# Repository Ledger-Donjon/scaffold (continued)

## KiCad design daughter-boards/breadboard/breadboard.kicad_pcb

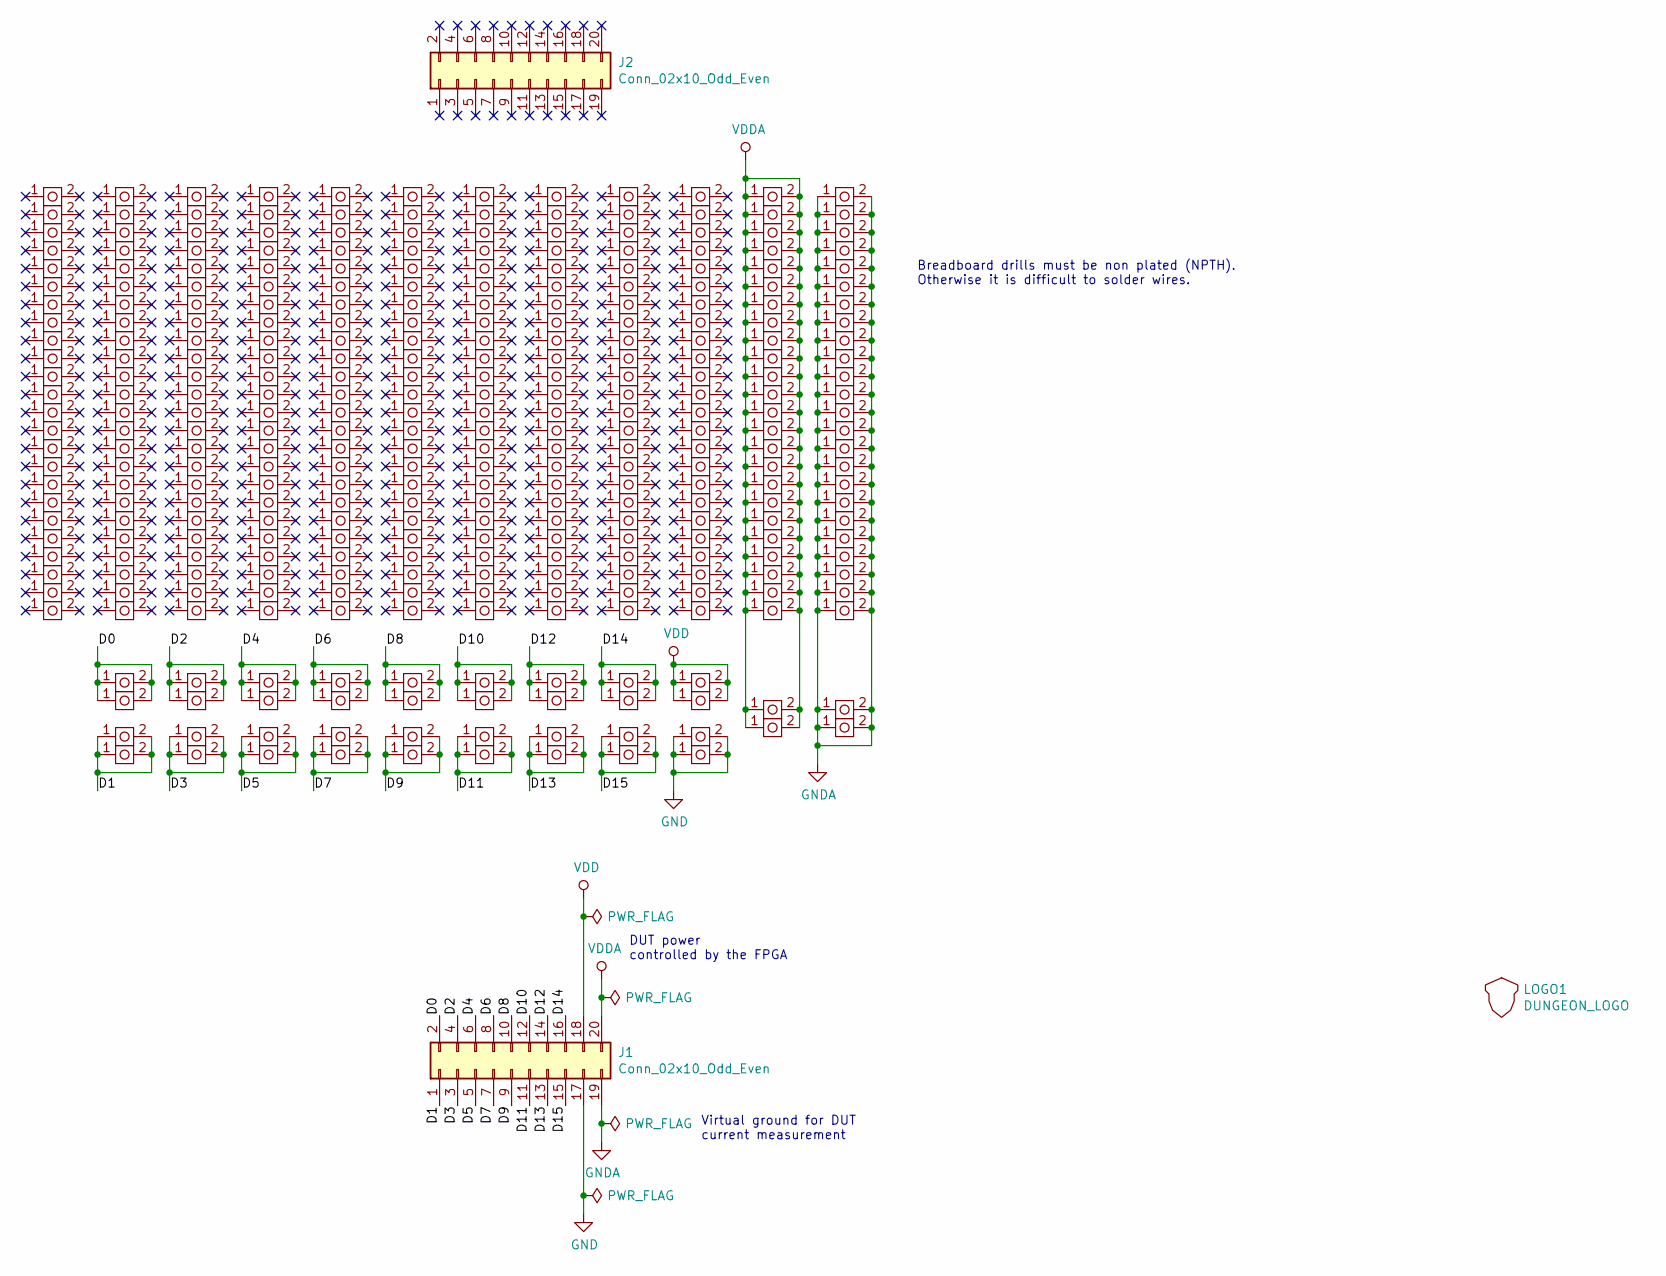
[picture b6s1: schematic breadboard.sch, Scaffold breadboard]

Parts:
J1, J2: Conn_02x10_Odd_Even; PinSocket_2x10_P2.54mm_Vertical
LOGO1: DUNGEON_LOGO; donjon-3000
U1, U2, U3, U4, U5, U6, U7, U8, U9, U10, U11, U12, U13, U14, U15, U16, U17, U18, U19, U20, U21, U22, U23, U24, U25, U26, U27, U28, U29, U30, U31, U32, U33, U34, U35, U36, U37, U38, U39, U40, U41, U42, U43, U44, U45, U46, U47, U48, U49, U50, U51, U52, U53, U54, U55, U56, U57, U58, U59, U60, U61, U62, U63, U64, U65, U66, U67, U68, U69, U70, U71, U72, U73, U74, U75, U76, U77, U78, U79, U80, U81, U82, U83, U84, U85, U86, U87, U88, U89, U90, U91, U92, U93, U94, U95, U96, U97, U98, U99, U100, U101, U102, U103, U104, U105, U106, U107, U108, U109, U110, U111, U112, U113, U114, U115, U116, U117, U118, U119, U120, U121, U122, U123, U124, U125, U126, U127, U128, U129, U130, U131, U132, U133, U134, U135, U136, U137, U138, U139, U140, U141, U142, U143, U144, U145, U146, U147, U148, U149, U150, U151, U152, U153, U154, U155, U156, U157, U158, U159, U160, U161, U162, U163, U164, U165, U166, U167, U168, U169, U170, U171, U172, U173, U174, U175, U176, U177, U178, U179, U180, U181, U182, U183, U184, U185, U186, U187, U188, U189, U190, U191, U192, U193, U194, U195, U196, U197, U198, U199, U200, U201, U202, U203, U204, U205, U206, U207, U208, U209, U210, U211, U212, U213, U214, U215, U216, U217, U218, U219, U220, U221, U222, U223, U224, U225, U226, U227, U228, U229, U230, U231, U232, U233, U234, U235, U236, U237, U238, U239, U240, U241, U242, U243, U244, U245, U246, U247, U248, U249, U250, U251, U252, U253, U254, U255, U256, U257, U258, U259, U260, U261, U262, U263, U264, U265, U266, U267, U268, U269, U270, U271, U272, U273, U274, U275, U276, U277, U278, U279, U280, U281, U282, U283, U284, U285, U286, U287, U288, U289, U290, U291, U292, U293, U294, U295, U296, U297, U298, U299, U300, U301, U302, U303, U304, U305, U306, U307, U308, U309, U310, U311, U312, U313, U314, U315, U316, U317, U318, U319, U320, U321, U322, U323, U324, U325, U326, U327, U328: BREADBOARD_NPTH; TEST_BREADBOARD_RECTANGULAR_NPTH2

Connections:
/D0: J1.2, U297.1, U297.2, U298.1, U298.2
/D1: J1.1, U299.1, U299.2, U300.1, U300.2
/D2: J1.4, U301.1, U301.2, U302.1, U302.2
/D3: J1.3, U303.1, U303.2, U304.1, U304.2
/D4: J1.6, U305.1, U305.2, U306.1, U306.2
/D5: J1.5, U307.1, U307.2, U308.1, U308.2
/D6: J1.8, U309.1, U309.2, U310.1, U310.2
/D7: J1.7, U311.1, U311.2, U312.1, U312.2
/D8: J1.10, U313.1, U313.2, U314.1, U314.2
/D9: J1.9, U315.1, U315.2, U316.1, U316.2
/D10: J1.12, U317.1, U317.2, U318.1, U318.2
/D11: J1.11, U319.1, U319.2, U320.1, U320.2
/D12: J1.14, U321.1, U321.2, U322.1, U322.2
/D13: J1.13, U323.1, U323.2, U324.1, U324.2
/D14: J1.16, U325.1, U325.2, U326.1, U326.2
/D15: J1.15, U327.1, U327.2, U328.1, U328.2
GND: J1.17, U295.1, U295.2, U296.1, U296.2
GNDA: J1.19, U267.1, U267.2, U268.1, U268.2, U269.1, U269.2, U270.1, U270.2, U271.1, U271.2, U272.1, U272.2, U273.1, U273.2, U274.1, U274.2, U275.1, U275.2, U276.1, U276.2, U277.1, U277.2, U278.1, U278.2, U279.1, U279.2, U280.1, U280.2, U281.1, U281.2, U282.1, U282.2, U283.1, U283.2, U284.1, U284.2, U285.1, U285.2, U286.1, U286.2, U287.1, U287.2, U288.1, U288.2, U289.1, U289.2, U290.1, U290.2, U291.1, U291.2, U292.1, U292.2
VDD: J1.18, U293.1, U293.2, U294.1, U294.2
VDDA: J1.20, U241.1, U241.2, U242.1, U242.2, U243.1, U243.2, U244.1, U244.2, U245.1, U245.2, U246.1, U246.2, U247.1, U247.2, U248.1, U248.2, U249.1, U249.2, U250.1, U250.2, U251.1, U251.2, U252.1, U252.2, U253.1, U253.2, U254.1, U254.2, U255.1, U255.2, U256.1, U256.2, U257.1, U257.2, U258.1, U258.2, U259.1, U259.2, U260.1, U260.2, U261.1, U261.2, U262.1, U262.2, U263.1, U263.2, U264.1, U264.2, U265.1, U265.2, U266.1, U266.2

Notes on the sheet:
Virtual ground for DUT current measurement
DUT power controlled by the FPGA
Breadboard drills must be non plated (NPTH). Otherwise it is difficult to solder wires.

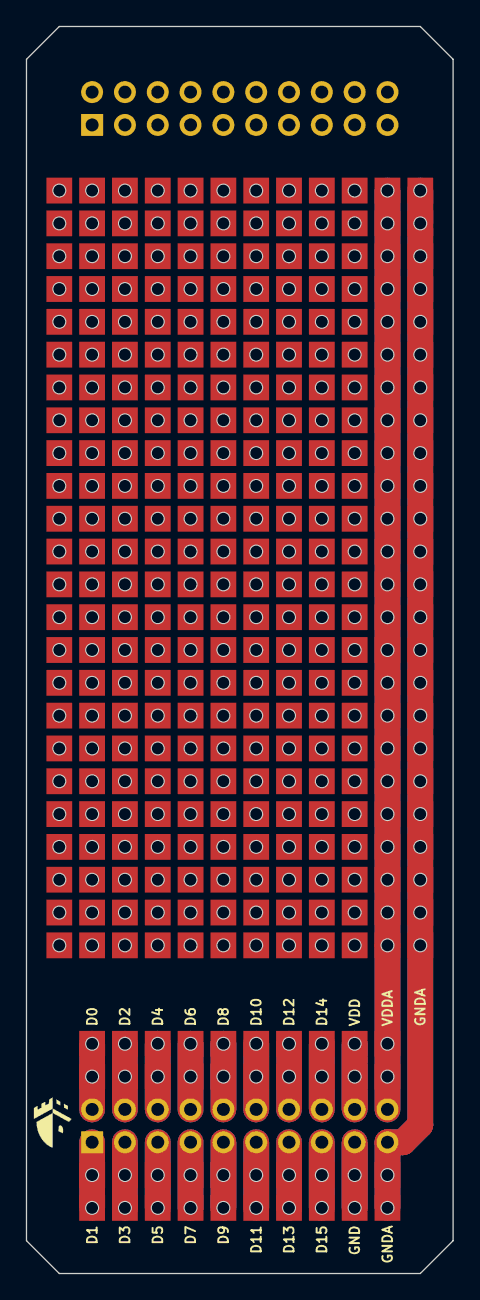
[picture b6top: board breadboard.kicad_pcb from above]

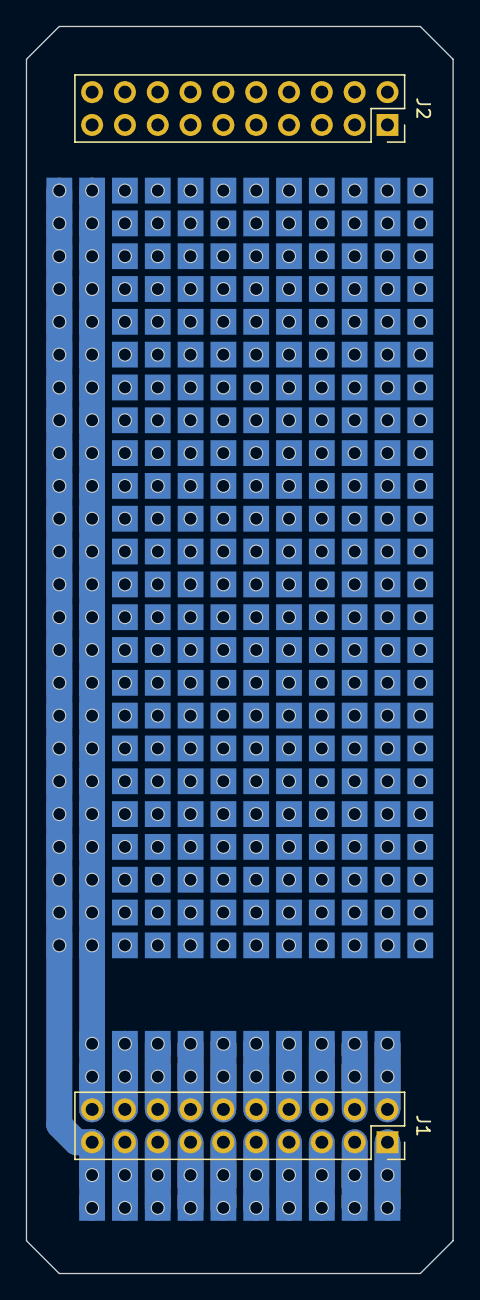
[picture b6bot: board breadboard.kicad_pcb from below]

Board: 2 copper layers, 33.0 x 96.5 mm, 331 parts (2 on the bottom side), 20 nets.

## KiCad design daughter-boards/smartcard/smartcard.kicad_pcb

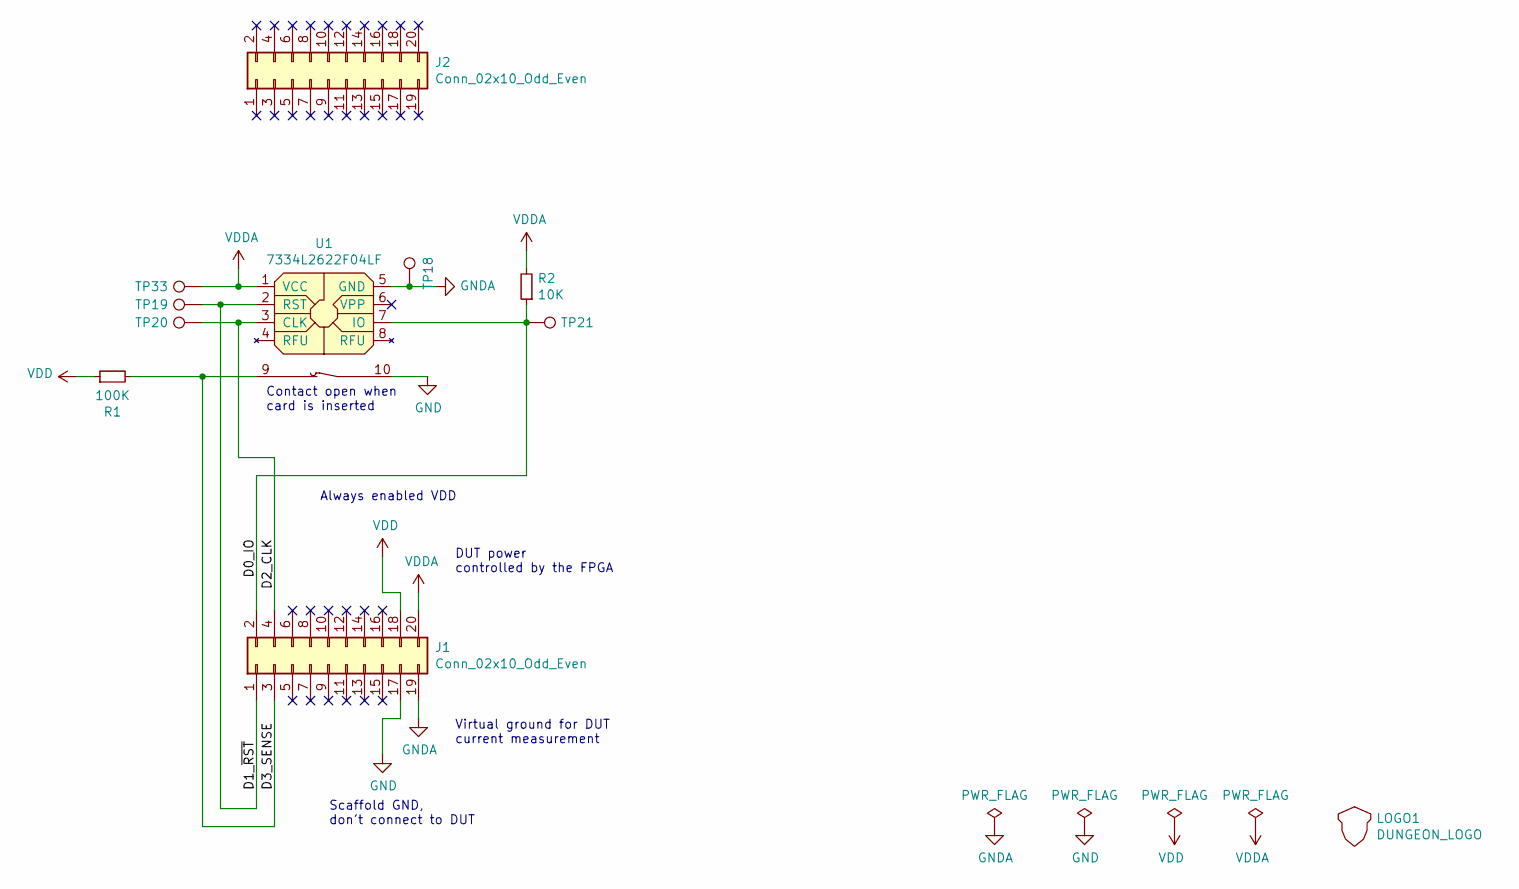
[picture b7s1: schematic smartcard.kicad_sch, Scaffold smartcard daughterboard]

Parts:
J1, J2: Conn_02x10_Odd_Even; PinSocket_2x10_P2.54mm_Vertical
LOGO1: DUNGEON_LOGO; donjon-2000
R1: 100K; R_0603_1608Metric
R2: 10K; R_0603_1608Metric
TP18, TP19, TP20, TP21, TP33: TestPoint; TestPoint_Pad_D1.5mm
U1: 7334L2622F04LF; AMPHENOL_SMARTCARD_7334L2622F04LF

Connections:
/D0_IO: J1.2, R2.1, TP21.1, U1.7 (IO)
/D1_~RST~: J1.1, TP19.1, U1.2 (RST)
/D2_CLK: J1.4, TP20.1, U1.3 (CLK)
/D3_SENSE: J1.3, R1.2, U1.9
GND: J1.17, U1.10
GNDA: J1.19, TP18.1, U1.5 (GND)
VDD: J1.18, R1.1
VDDA: J1.20, R2.2, TP33.1, U1.1 (VCC)

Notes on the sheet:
Virtual ground for DUT current measurement
DUT power controlled by the FPGA
Contact open when card is inserted
Scaffold GND, don't connect to DUT
Always enabled VDD

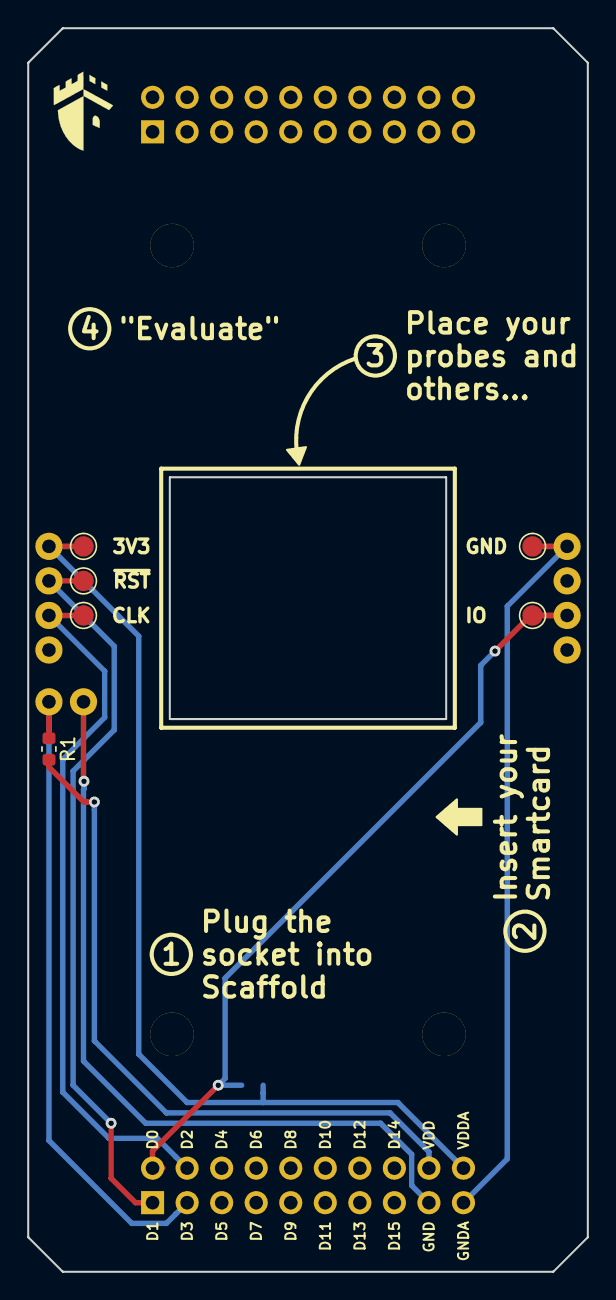
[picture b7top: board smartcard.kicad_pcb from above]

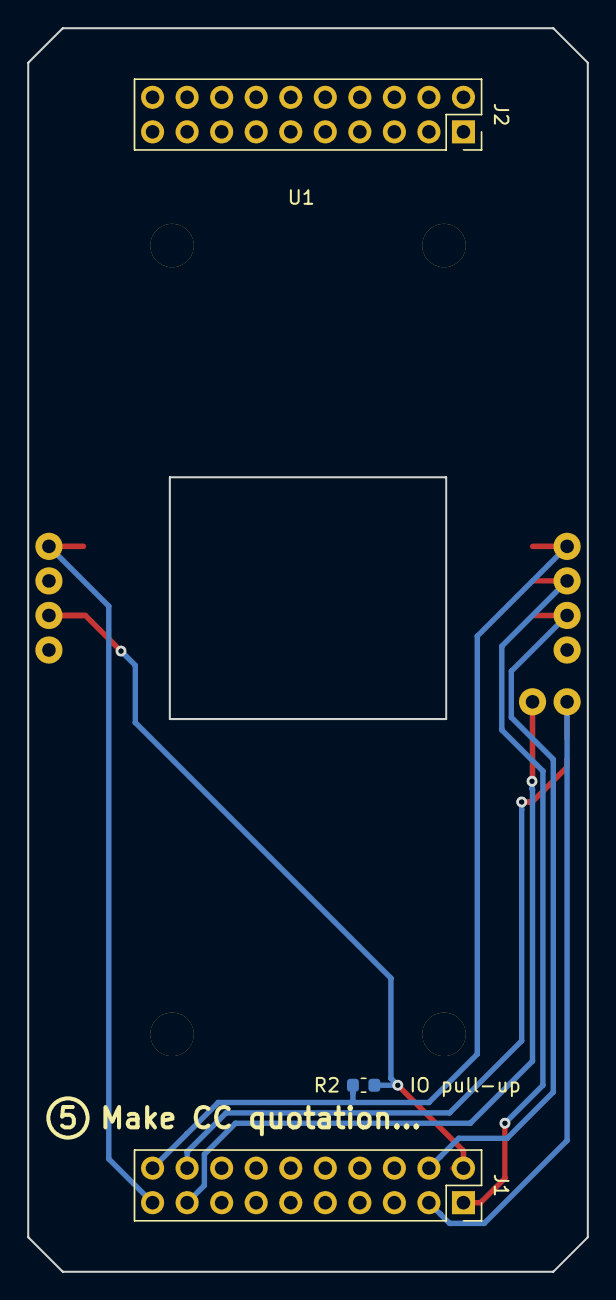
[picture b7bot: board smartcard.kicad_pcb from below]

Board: 2 copper layers, 41.1 x 91.4 mm, 11 parts (4 on the bottom side), 8 nets.

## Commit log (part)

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2019-03-28 Initialized repository with license and readme.
2019-03-29 Added FPGA architecture VHDL files.
2019-03-29 Added API and examples.
2019-03-29 Documentation fixes
    Added requirements file for rtd.io.
    Fixed JSON format for wavedrom figures.
2019-03-29 Fixed example in documentation.
2019-03-29 Refactoring on pulse generators.
    Renammed delay_1 to delay and delay_2 to interval.
2019-04-01 Update kit_smartcard.rst: typo from text copy
2019-04-01 Added rtd badge in readme.
2019-04-02 Minor fixes in documentation.
2019-04-03 Refactored I/Os in VHDL architecture.
    There is now one module for each I/O. Each module has a separate value
    register with a unique address. This will allow implementing more
    features for the I/Os.
    Architecture version is now 0.3.
    The API has been updated and should work with 0.2 and 0.3 versions.
    Better implementation for scaffold registers initialization: each
2019-04-04 Added mode configuration in I/Os.
2019-04-04 Minor update in readme.
2019-04-04 Implemented IO modes in API.
2019-04-04 More info in TimeoutError.
    The number of expected processed bytes is now included in the
    TimeoutError exception.
2019-04-04 PEP8
2019-04-09 Faster I2C transaction management in API.
    I2C transaction readout was performed with active polling on API side.
    Polling is now performed on hardware side.
2019-04-09 Minor refactoring on timeout control in API.
2019-04-12 Updated readme.
2019-04-19 I/Os initialization is now optional.
2019-05-09 Added board status notice in readme.
2019-05-09 Renammed fab folders to gerber.
2019-05-22 Updated STM32 example script.
    Added options to load and execute code into RAM memory.
2019-05-28 Improvement in signals management in API.
    A source signal can now have the same name as a destination signal
    without ambiguity. This may allow connecting peripheral outputs to
    peripheral inputs if hardware supports it.
2019-05-28 Removed debug print.
2019-07-16 Updated board status in readme.
2019-07-23 Updated daughterboards for the new Scaffold socket
    Update breadboard, smartcard and STM32F205 daughterboards to fit the
    new socket format of Scaffold v1.1 hardware.
    Previous socket format is now deprecated.
2019-08-01 Added support for pull resistors.
    Updated VHDL code to drive pull resistors of Scaffold v1.1.
    Updated API to allow configuration of the pull resistors.
    Updated documentation.
    Architecture version is now 0.5.
2019-08-07 Fixed incorrect pin assignment for D3.
2019-08-07 Updated documentation.
2019-08-09 Added STM32F427 daughterboard.
2019-08-09 Minor documentation edit.
2019-08-19 Fixed FPGA pin configuration.
2019-08-20 Added missing UART parity property in API.
2019-08-20 Minor documentation update.
2019-09-05 Added SPI peripheral draft.
    First VHDL draft of SPI peripheral. Not tested yet, has bugs for sure.
2019-09-05 Added trigger chain module.
2019-09-06 Fixed doc generation issue.
2019-09-06 Added missing VHDL files.
2019-09-09 Added clock generation module.
2019-09-10 Updated clock module API.
2019-09-10 API fix for SPI peripheral.
2019-09-10 Updated readme for a better project description.
2019-09-11 Added VHDL simulation test-bench.
    The provided simulation file can be used to simulate all the
    architecture. Some assertions are also present for testing and
    detecting regressions.
    Code coverage is not very high but this test is still of helpful and
    can be be used for debugging as well.
2019-09-17 Updates in API.
    Better property names for the clock module.
    Added restart_dut, restart_platform and restart_all methods in power
    module.
2019-09-24 Fixed bug in API introduced in previous commit.
2019-10-08 Minor edit for pypi packaging.
2019-10-22 Fixed holes in breadboard daughterboard.
    Replaced plated holes with non-plated holes for easier solderability.
2020-02-03 Minor changes
    Typo fix in scaffold.sdc
    Python API: adding a signal in a module now returns the created Signal
    object.
2020-02-10 Configurable PulseGenerator base address
2020-02-18 Added min/max properties in PulseGenerator class
2020-02-26 Bug fix in timeouts
2020-02-27 Fixed bug in ISO7816
    When receiving an invalid procedure byte, the apdu method was
    returning None. A RuntimeError exception is now thrown.
2020-02-27 Implemented basic PPS request method for ISO7816
2020-03-16 Automatic board detection
    Added script to configure Scaffold board USB description string (FTDI
    EEPROM programming).
    Added automatic detection of the board when no device is specified.
2020-07-29 Added triggering option in ISO7816.transmit
2021-01-06 Fixed board autodetection
2021-03-19 Added some commands to STM32 bootloader client
2021-05-06 Fixed FIFO queue overflow with Scaffold API
    In lazy write operations, the API now blocks on pending write
    operations when the hardware FIFO buffer may overflow.
2021-07-12 Fixed minor doc issue on PPS request for ISO7816
    The byte for selecting speed during PPS negociation is PPS1, not PPS0.
2021-07-12 Fix #3: errors in documentation example
2021-07-16 Fix #5: ATR database miss and fallback
    Raising NoATRDatabase exception when ATR database cannot be obtained.
    When allowed, downloads the ATR database from the web as a fallback if
    the database file is missing from the filesystem.
2021-07-21 Added serial number matching for board detection
    This new feature can be used to connect to the right board without
    worrying about serial device paths when multiple Scaffold boards are
    available.
2021-07-21 Continuous Integration configuration for Flake8
2021-07-21 Switch from unittest to pytest
2021-07-21 Fixed ATR parsing test
2021-07-26 Basic support for T=1 smartcard protocol
2021-07-26 Fixed requirements for documentation build
2021-07-26 Documentation
2021-07-29 Updated FPGA compiled bitstream
2021-08-23 Fixed bus bridge bug on read operations
2021-08-26 Fixed minor bug in Smartcard class
2021-12-02 A0 to A3 board outputs now defaults to 0V
    When board is powered on or reset, A0 to A3 outputs now drive the
    signal to 0 instead of 3.3V or 5V.
2021-12-09 Fixes in timeout management
    Pushing a new timeout value cannot increase currently defined timeout.
2022-01-24 Minor fix in documentation
2022-03-18 Support for ISO7816 T=1 blocks chaining
2022-10-14 Remove warnings when creating the doc.
2022-10-14 Use wavedrompy as alternative, to prevent failure on readthedocs
2022-10-14 Solving issue #11
2023-05-05 Correction ajout STM32 F100
2023-05-05 Added STM32 F100 (#13)
    STM32 F100 added
2023-09-04 SPI slave mode support
2023-10-10 Added STM32U59x/5Ax in known devices
2023-11-29 Added ESP32 daughterboard
2023-12-05 Bump python library version
2024-01-25 Added .flake8 configuration file
2024-01-25 Fixed ISO7816 ATR parsing test vectors
2024-01-29 Added delays and buffer wait to the architecture
    Added two new operations to the Scaffold hardware architecture:
    - delay: wait for a given number of clock cycles
    - buffer wait: block execution until buffer has enough data
    Refactored commands management to increase performances: responses from
    the board are fetched as late as possible. This should make lazy
    sections obsoletes.
2024-01-29 Minor fixes
    Added version checking if delay or buffer wait is used.
    delay now accepts duration in seconds.
2024-01-29 Moved bus related classes to bus.py
    __init__.py is a very big files. ScaffoldBus, ScaffoldBusTimeoutSection
    and Register classes have been moved to bus.py to improve code
    organization.
2024-01-30 Added FIFO buffer for transmission UART
    Added a FIFO buffer which stores the response bytes to be transmitted,
    which can improve board commands processing speed.
2024-02-01 Added buffer wait operations and some refactoring
    Added methods to use buffer wait operations.
    Created classes for each kind of bus operation: ReadOperation,
    WriteOperation, TimeoutOperation, DelayOperation, BufferWaitOperation.
2024-02-01 Refactoring in polling management
    Added Polling class which regroups polling parameters, instead of
    passing them all as function arguments.
2024-02-01 Fix for flake8
2024-02-06 Fixed issue with bus operations deletion
2024-03-07 Update STM32 script
2024-03-09 Type annotation improvement, formatting, slight changes in documentation
2024-03-09 Make type checker aware of signals and registers (unless just relying on the dynamic population of __dict__) Far less elegant for readability and risks of typo errors, but did not found any workaroun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
2024-03-09 Modification of registers directly by assigning values confuses type checkers, which annotate them as 'int'
2024-03-09 Update continuous-integration.yml
    Usage of actions/checkout@v3 to remove warning
    "The following actions uses node12 which is deprecated and will be forced to run on node16"
2024-03-09 Prevent undefined symbol error
2024-05-29 Fixed version comparison issue
2024-05-31 Make flake8 happier
2024-05-31 Fix typo in the calculation of the parity bit for reads
2024-07-17 Use version 10.0
2024-07-22 Remove useless comments
2024-07-30 Better comments
2024-08-27 Take review comments into account for the API
2024-08-30 Fixing #23
2024-08-30 Bump version 10.0
2024-09-03 Use to_bytes for splitting wdata, as per review recommendation
2024-09-03 Fix typo, as per review comment
2024-09-03 Prefer mkRegA to mkReg
2024-09-05 Add trigger output
2024-09-05 Satisfy linter
2024-09-17 Create a I2CTrigger Flag type
2024-09-19 Type checking update
2024-09-19 Fix linting problems
2024-09-19 Correction of linter issues
2024-09-19 Resolve import issue
2024-09-20 locking configuration and data take time for ACK
2024-09-23 Update Info command
2025-01-15 Add type annotations
2025-01-15 Remove name parameter from add_register
2025-01-16 Fix newline issue in .gitignore
2025-01-16 Update test according to database update: Add failing elements in database change the parsing retrieval method permit to download the database
2025-01-16 Fix linting failures, revert filtering in test
2025-01-16 Fix ATR comparision (bytes / str)
2025-01-17 Taking into account remarks from first review
2025-01-17 flake8 not passing
2025-01-17 pyproject.toml Usage
2025-04-21 Decoding Redundancy code for T=1 Fixes #30
2025-05-21 Added ISO-14443-A support.
    Added ISO-14443-A Scaffold peripheral and associated NFC daughterboard
    based on TRF7970A chip.
2025-05-22 ISO-14443 carrier clock synchronization
    ISO-14443 transmitter can now resynchronize on the 13.56 MHz carrier
    clock to reduce jitter.
2025-06-16 Refactored ISO-14443 peripheral VHDL
    Reworked how reception is done: we now have a demodulation stage whose
    output is used for synchronization and decoding. This implementation is
    much more reliable and works when response takes time to start. As we
    are not sampling the subcarrier anymore, this is more tolerant to
    jitter.
2025-06-16 Minor update in readme
2025-06-17 Updated bitstream file
2025-06-17 Minor bug fix
2025-06-20 Optimization fine tuning for ISO-14443
    Tweaks to slightly reduce ISO-14443 Scaffold response reading time.
2025-07-01 Refactor code structure for improved readability and maintainability
2025-07-01 Add support of WTX requests from cards in ISO7816 T1 protocol (#34)
    * Add support of WTX requests from cards in ISO7816 T1 protocol
    Fixes #33
    * Refactor code structure for improved readability and maintainability
    * Bump to version 0.9.5
2025-07-02 feat(cli): support uart
2025-07-03 feat(cli): add color on all subcommands help
2025-07-03 docs(issue33) Add a note about trigger assertion
2025-07-03 refactor(cli): change IO state for on/off to high/low
2025-07-04 Update pyproject and move cli file into scaffold folder
2025-07-21 docs: fix getting started codeblock
2025-07-25 fix(iso14443): reset the block number during startup
2025-08-04 fix(iso14443): timing issue on first symbol
2025-10-02 doc(daughterboards):Update Kicad daugtherboard/smartcard project and fix typo in schematics
2025-10-10 fix(daugtherboard): update the schematics after modification of STM32 symbol from Kicad update
2025-11-27 Increased FPGA RX buffer size
